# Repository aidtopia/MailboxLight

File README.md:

# MailboxLight
An LED that illuminates the inside of the mailbox when the door is opened.

by Adrian McCarthy

This was a very simple project I undertook to learn how to use KiCAD to design a printed circuit board.  The fact that I can now see all the mail in my mailbox when I check it at night is a nice bonus.

You're welcome to make these yourself or to fork and modify them to better suit your own requirements.  Since this was just a learning project for me, I probably won't bother responding to pull-requests.

No warranty.  No claims of fitness for any purpose.  Use at your own risk.

## Assembly Notes

The specified value for R1 is 15 Ohms, which would yield the brightest light, but it's not a standard resistor value.  I used 22 Ohms in mine, which worked out fine.  The CR2032 battery lasted approximately one year of usage.

Rather than mounting the LED flush with the board, you might want to mount it a few millimeters above the board, which would allow you to bend the leads so that the LED points toward the back of the mailbox when mounted.

## Mounting

The mounting plate can be rendered to STL with OpenSCAD.  Use your favorite slicer to generate the appropriate file for your 3D printer.  It's very simple and should work just fine with all of the default settings.  I used the Cura slicer with an Ultimaker 2 and PLA filament.

The PCB can be secured to the mounting plate with 8mm long M2 machine screws and nuts.  (The nuts fit into recesses in the back of the plate.)  The device can then be attached to the side of the mailbox, just behind the door, using double-sided tape.  For me, 3M Command-brand mounting tape worked perfectly, but any double-sided foam tape should also work.  Follow your tape's instructions for best adhesion.

The lever arm of the switch is too short, so it's important to mount it as close as possible to the threshold.  Even so, you might want to mount a small square of cardboard or foam tape to the inside of the door to ensure the switch is fully depressed when the door is closed.

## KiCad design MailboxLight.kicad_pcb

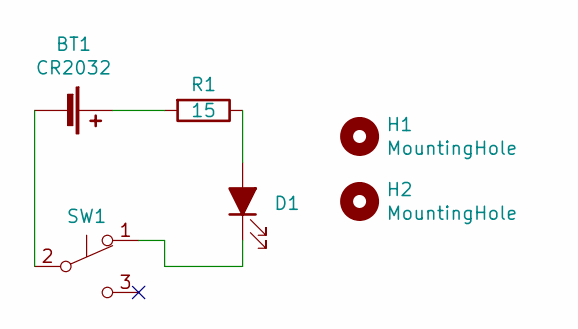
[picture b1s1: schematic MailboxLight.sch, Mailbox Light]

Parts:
BT1: CR2032; BatteryHolder_MPD_BS-5_1x2032_vertical; Digi-Key BS-5-ND
D1: LED_ALT; LED_D10.0mm
H1, H2: MountingHole; MountingHole_2.2mm_M2
R1: 15; R_Axial_DIN0207_L6.3mm_D2.5mm_P7.62mm_Horizontal
SW1: SW_SPDT; SW_Snap_SPDT_Omron_D2F-01FL2-A1; Digi-Key Z4697-ND

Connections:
unnamed: BT1.1 (+), R1.2
unnamed: BT1.2 (-), SW1.2 (B)
unnamed: D1.1 (K), SW1.1 (A)
unnamed: D1.2 (A), R1.1

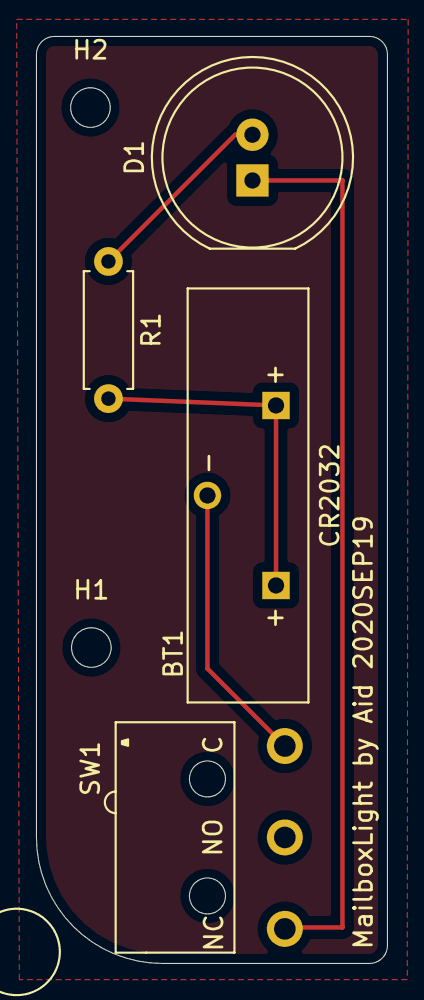
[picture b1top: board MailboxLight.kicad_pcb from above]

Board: 2 copper layers, 19.5 x 51.5 mm, 6 parts (0 on the bottom side), 4 nets.

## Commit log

2020-09-20 Initial design.
2020-09-20 Still learning how to coordinate between local git and Github.
2021-10-04 NFC: fixed typo in a comment
2021-10-04 Last-minute changes to PCB file wasn't committed back then.
    Also updated .gitignore to ignore more generated files.
2021-10-04 Added notes to README.md
